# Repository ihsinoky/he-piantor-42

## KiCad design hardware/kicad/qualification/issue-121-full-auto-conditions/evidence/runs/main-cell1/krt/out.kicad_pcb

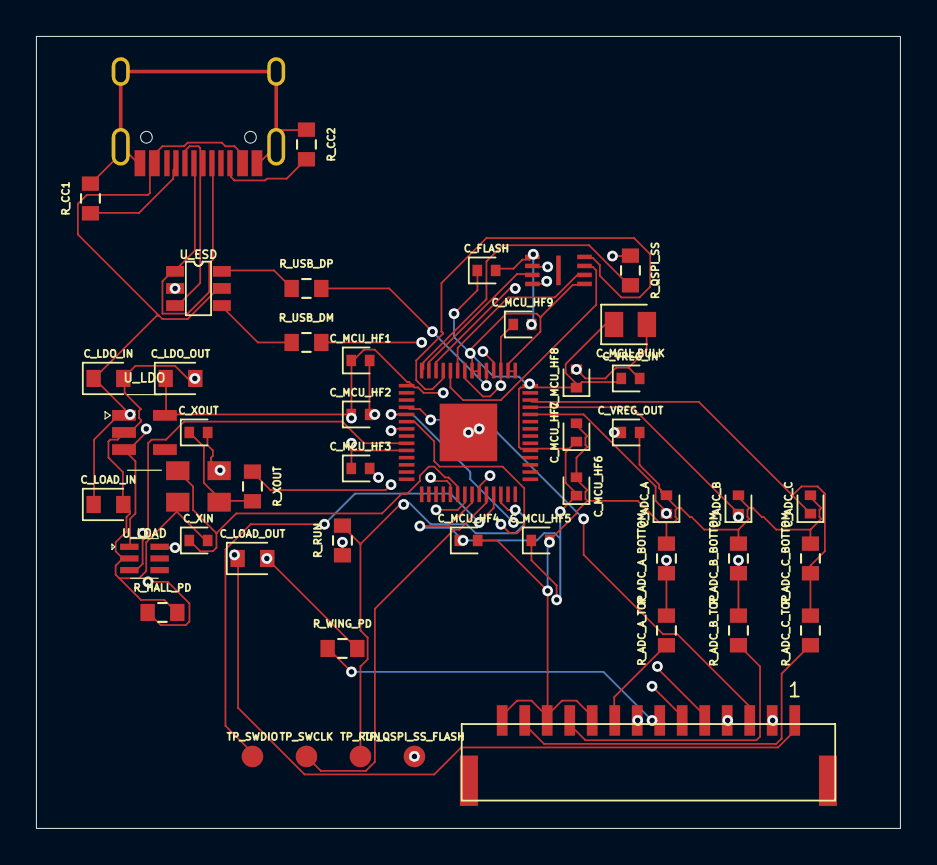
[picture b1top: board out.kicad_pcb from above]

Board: 4 copper layers, 48.0 x 44.0 mm, 49 parts (0 on the bottom side), 37 nets.

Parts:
C1: 15pF; C1
C2: 15pF; C2
C3: 100nF; C3
C4: 100nF; C4
C5: 100nF; C5
C6: 100nF; C6
C7: 100nF; C7
C8: 100nF; C8
C9: 100nF; C9
C10: 100nF; C10
C11: 100nF; C11
C12: 1uF; C12
C13: 1uF; C13
C14: 10uF; C14
C15: 100nF; C15
C16: 1uF; C16
C17: 1uF; C17
C18: 1uF; C18
C19: 1uF; C19
C20: 1nF; C20
C21: 1nF; C21
C22: 1nF; C22
J1: TYPE-C-31-M-12; J1
J2: BM14B-GHS-TBT(LF)(SN); J2
R1: 5.1k; R1
R2: 5.1k; R2
R3: 27; R3
R4: 27; R4
R5: 1k; R5
R6: 100k; R6
R7: 100k; R7
R8: 10k; R8
R9: 1k; R9
R10: 6.8k; R10
R11: 10k; R11
R12: 6.8k; R12
R13: 10k; R13
R14: 6.8k; R14
R15: 10k; R15
TP1: TestPoint; TP1
TP2: TestPoint; TP2
TP3: TestPoint; TP3
TP4: TestPoint; TP4
U1: RP2040; U1
U2: USBLC6-2SC6; U2
U3: W25Q16JVUXIQ; U3
U4: AP2112K-3.3TRG1; U4
U5: TPS22919DCKR; U5
Y1: ABM8-272-T3; Y1

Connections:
ADC_A: C20.1, R10.2, R11.1, U1.38
ADC_B: C21.1, R12.2, R13.1, U1.39
ADC_C: C22.1, R14.2, R15.1, U1.40
CC1: J1.3, R1.1
CC2: J1.10, R2.1
GND: C1.2, C2.2, C3.2, C4.2, C5.2, C6.2, C7.2, C8.2, C9.2, C10.2, C11.2, C12.2, C13.2, C14.2, C15.2, C16.2, C17.2, C18.2, C19.2, C20.2, C21.2, C22.2, J1.1, J1.12, J1.13, J2.2, J2.4, J2.8, J2.10, J2.12, J2.14, R1.2, R2.2, R6.2, R7.2, R11.2, R13.2, R15.2, U1.19, U1.57, U2.2, U3.4, U4.2, U5.2, Y1.2, Y1.4
HALL_5V: C19.1, J2.1, U5.6
HALL_PWR_EN: R7.1, U1.9, U5.3
MUX_A0: J2.3, U1.4
MUX_A1: J2.5, U1.5
MUX_A2: J2.6, U1.6
MUX_OUT_A: J2.9, R10.1
MUX_OUT_B: J2.11, R12.1
MUX_OUT_C: J2.13, R14.1
QSPI_SCLK: U1.52, U3.6
QSPI_SD0: U1.53, U3.5
QSPI_SD1: U1.55, U3.2
QSPI_SD2: U1.54, U3.3
QSPI_SD3: U1.51, U3.7
QSPI_SS_FLASH: R5.2, TP4.1, U3.1
QSPI_SS_MCU: R5.1, U1.56
RUN: R8.2, TP3.1, U1.26
SWCLK: TP2.1, U1.24
SWDIO: TP1.1, U1.25
USB_DM: R4.2, U1.46
USB_DM_CONN: J1.5, J1.8, U2.3
USB_DM_ESD: R4.1, U2.4
USB_DP: R3.2, U1.47
USB_DP_CONN: J1.4, J1.9, U2.1
USB_DP_ESD: R3.1, U2.6
V1V1: C11.1, C13.1, U1.23, U1.45, U1.50
V3V3: C3.1, C4.1, C5.1, C6.1, C7.1, C8.1, C9.1, C10.1, C12.1, C14.1, C15.1, C17.1, R8.1, U1.1, U1.10, U1.22, U1.33, U1.42, U1.43, U1.44, U1.48, U1.49, U3.8, U4.5
VBUS: C16.1, C18.1, J1.2, J1.11, U2.5, U4.1, U4.3, U5.1
WING_EN: J2.7, R6.1, U1.7
XIN: C1.1, U1.20, Y1.1
XOUT: R9.2, U1.21
XOUT_XTAL: C2.1, R9.1, Y1.3

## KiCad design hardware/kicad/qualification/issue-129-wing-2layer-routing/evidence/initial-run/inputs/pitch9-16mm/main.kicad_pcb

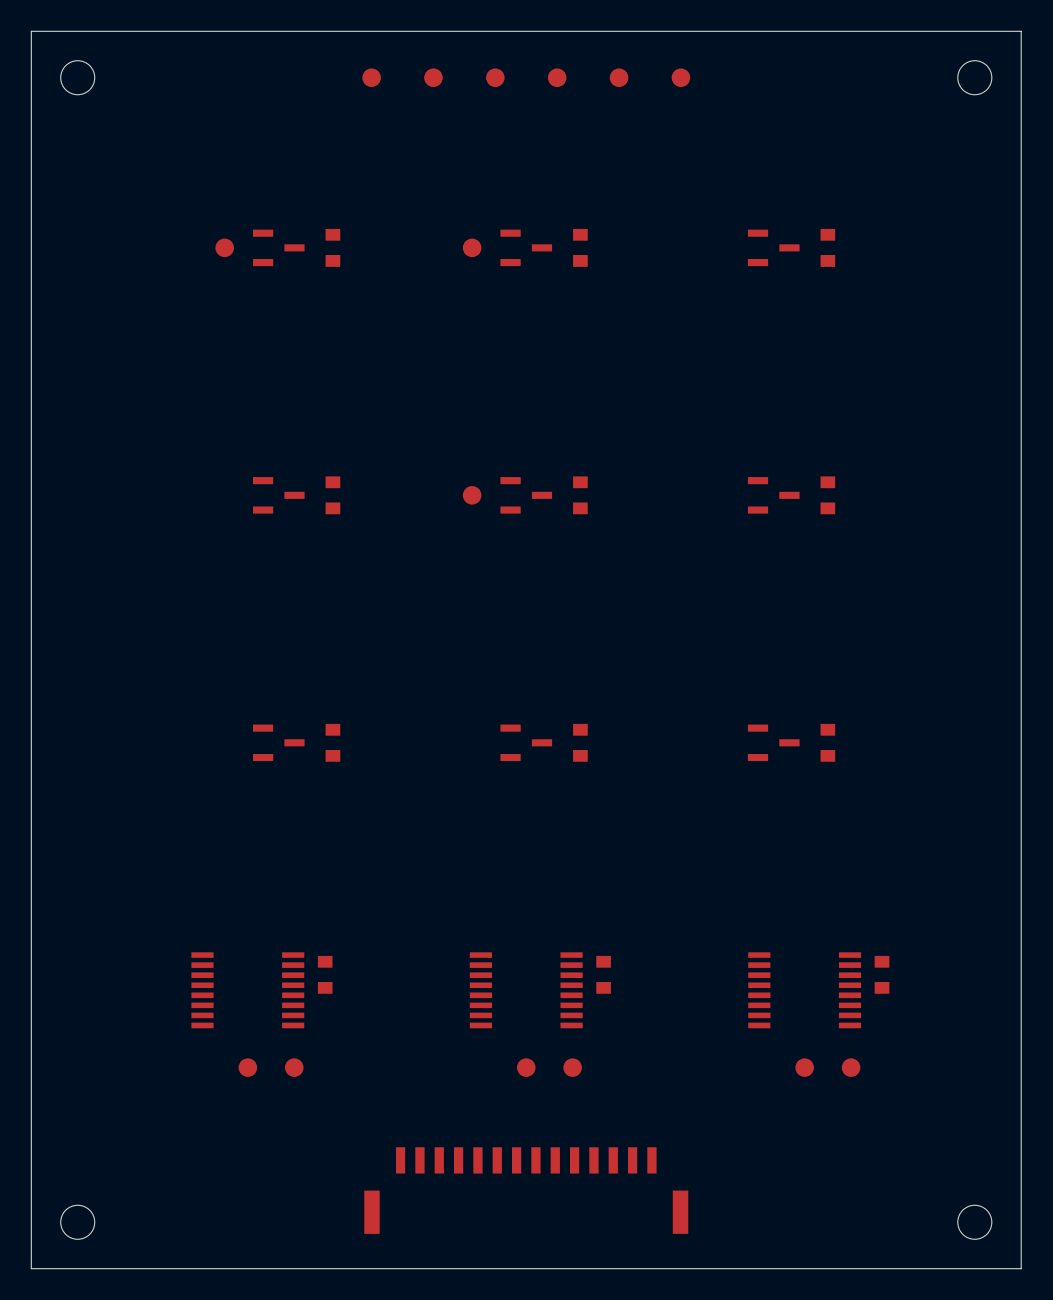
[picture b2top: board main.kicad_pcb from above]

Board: 2 copper layers, 64.0 x 80.0 mm, 44 parts (0 on the bottom side), 18 nets, no tracks yet.

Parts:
C_HA0, C_HA1, C_HA2: GRM188R71C104KA01D; capacitor
C_HB0, C_HB1, C_HB2: GRM188R71C104KA01D; capacitor
C_HC0, C_HC1, C_HC2: GRM188R71C104KA01D; capacitor
C_MUX_A: GRM188R71C104KA01D; capacitor
C_MUX_B: GRM188R71C104KA01D; capacitor
C_MUX_C: GRM188R71C104KA01D; capacitor
H1, H2, H3, H4: NPTH_2.2mm; mounting
J_WING: BM14B-GHS-TBT(LF)(SN); connector
TP_H_CTR_RAW: PCB_PAD_1.2MM; testpoint
TP_H_DIAG_RAW: PCB_PAD_1.2MM; testpoint
TP_H_N_RAW: PCB_PAD_1.2MM; testpoint
TP_W_A0, TP_W_A1, TP_W_A2: PCB_PAD_1.2MM; testpoint
TP_W_EN: PCB_PAD_1.2MM; testpoint
TP_W_GND: PCB_PAD_1.2MM; testpoint
TP_W_GND_A: PCB_PAD_1.2MM; testpoint
TP_W_GND_B: PCB_PAD_1.2MM; testpoint
TP_W_GND_C: PCB_PAD_1.2MM; testpoint
TP_W_H5V: PCB_PAD_1.2MM; testpoint
TP_W_MUXA: PCB_PAD_1.2MM; testpoint
TP_W_MUXB: PCB_PAD_1.2MM; testpoint
TP_W_MUXC: PCB_PAD_1.2MM; testpoint
U_HA0, U_HA1, U_HA2: DRV5055A3QDBZR; hall
U_HB0, U_HB1, U_HB2: DRV5055A3QDBZR; hall
U_HC0, U_HC1, U_HC2: DRV5055A3QDBZR; hall
U_MUX_A: TMUX1208PWR; mux
U_MUX_B: TMUX1208PWR; mux
U_MUX_C: TMUX1208PWR; mux

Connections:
GND: C_HA0.2, C_HA1.2, C_HA2.2, C_HB0.2, C_HB1.2, C_HB2.2, C_HC0.2, C_HC1.2, C_HC2.2, C_MUX_A.2, C_MUX_B.2, C_MUX_C.2, J_WING.2, J_WING.4, J_WING.8, J_WING.10, J_WING.12, J_WING.14, TP_W_GND.1, TP_W_GND_A.1, TP_W_GND_B.1, TP_W_GND_C.1, U_HA0.3, U_HA1.3, U_HA2.3, U_HB0.3, U_HB1.3, U_HB2.3, U_HC0.3, U_HC1.3, U_HC2.3, U_MUX_A.14, U_MUX_B.14, U_MUX_C.14
HALL_5V: C_HA0.1, C_HA1.1, C_HA2.1, C_HB0.1, C_HB1.1, C_HB2.1, C_HC0.1, C_HC1.1, C_HC2.1, C_MUX_A.1, C_MUX_B.1, C_MUX_C.1, J_WING.1, TP_W_H5V.1, U_HA0.1, U_HA1.1, U_HA2.1, U_HB0.1, U_HB1.1, U_HB2.1, U_HC0.1, U_HC1.1, U_HC2.1, U_MUX_A.13, U_MUX_B.13, U_MUX_C.13
H_A0_RAW: TP_H_DIAG_RAW.1, U_HA0.2, U_MUX_A.4
H_A1_RAW: U_HA1.2, U_MUX_A.5
H_A2_RAW: U_HA2.2, U_MUX_A.6
H_B0_RAW: TP_H_N_RAW.1, U_HB0.2, U_MUX_B.4
H_B1_RAW: TP_H_CTR_RAW.1, U_HB1.2, U_MUX_B.5
H_B2_RAW: U_HB2.2, U_MUX_B.6
H_C0_RAW: U_HC0.2, U_MUX_C.4
H_C1_RAW: U_HC1.2, U_MUX_C.5
H_C2_RAW: U_HC2.2, U_MUX_C.6
MUX_A0: J_WING.3, TP_W_A0.1, U_MUX_A.1, U_MUX_B.1, U_MUX_C.1
MUX_A1: J_WING.5, TP_W_A1.1, U_MUX_A.16, U_MUX_B.16, U_MUX_C.16
MUX_A2: J_WING.6, TP_W_A2.1, U_MUX_A.15, U_MUX_B.15, U_MUX_C.15
MUX_OUT_A: J_WING.9, TP_W_MUXA.1, U_MUX_A.8
MUX_OUT_B: J_WING.11, TP_W_MUXB.1, U_MUX_B.8
MUX_OUT_C: J_WING.13, TP_W_MUXC.1, U_MUX_C.8
WING_EN: J_WING.7, TP_W_EN.1, U_MUX_A.2, U_MUX_B.2, U_MUX_C.2
